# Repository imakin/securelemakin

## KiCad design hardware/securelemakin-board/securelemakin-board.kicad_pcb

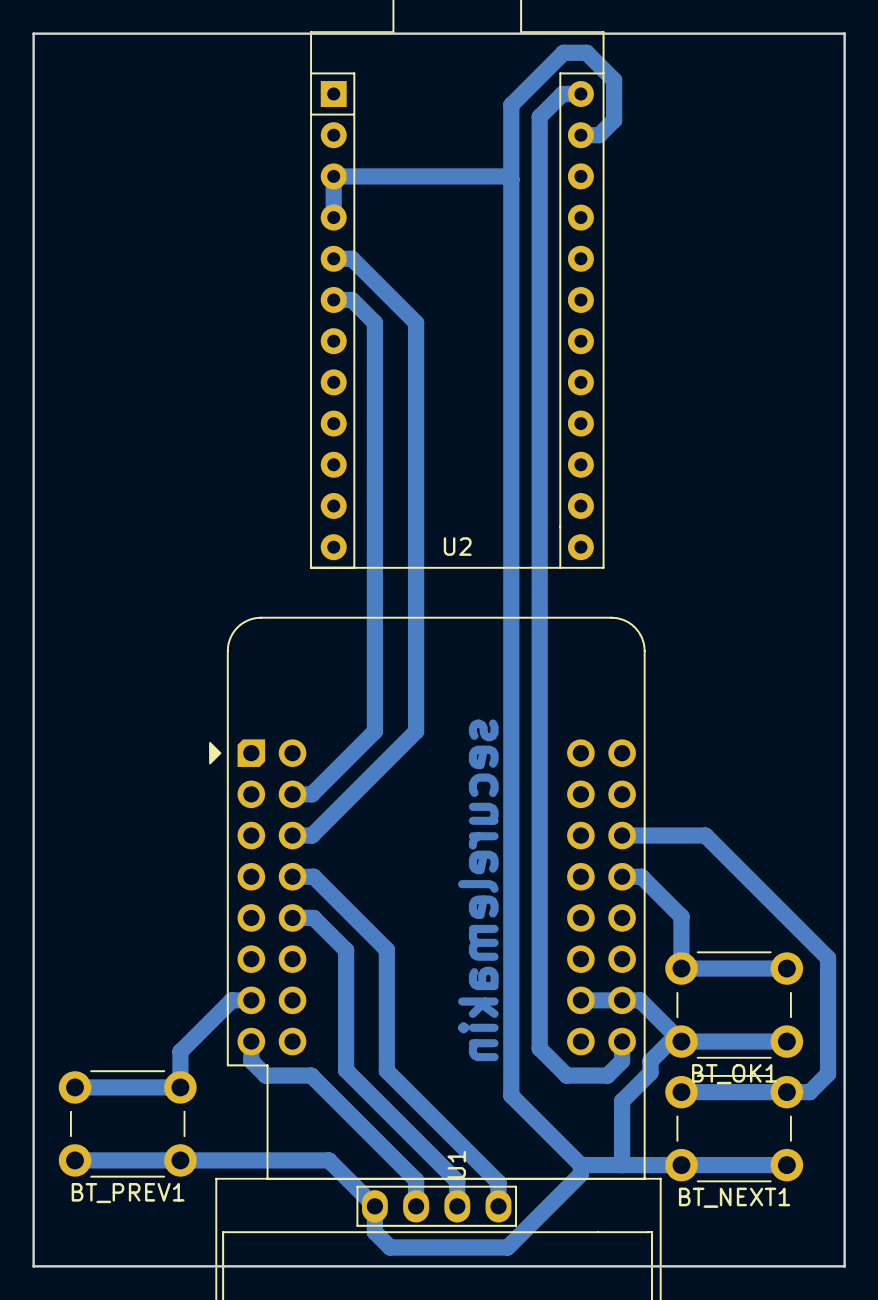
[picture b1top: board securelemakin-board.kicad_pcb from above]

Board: 2 copper layers, 50.0 x 76.0 mm, 6 parts (0 on the bottom side), 10 nets.

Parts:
BT_NEXT1: SW_Push; SW_PUSH_6mm
BT_OK1: SW_Push; SW_PUSH_6mm
BT_PREV1: SW_Push; SW_PUSH_6mm
Brd1: SSD1306; 128x64OLED
U1: WeMos_S2_mini; WEMOS_S2_mini
U2: Sparkfun_Pro_Micro

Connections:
/SCL: U1.18 (GPIO2), U2.6 (~D3)
/SCL_SSD1306: Brd1.3 (SCL), U1.21 (GPIO8)
/SDA: U1.19 (GPIO4), U2.5 (D2)
/SDA_SSD1306: Brd1.4 (SDA), U1.20 (GPIO6)
Earth: BT_NEXT1.1, BT_OK1.1, BT_PREV1.1, Brd1.1 (GND), U1.10 (GND), U1.26 (GND), U2.3 (GND), U2.4 (GND), U2.23 (GND)
unnamed: Brd1.2 (VCC), U1.8 (3V3)
unnamed: BT_PREV1.2, U1.7 (GPIO12)
unnamed: BT_OK1.2, U1.13 (GPIO33)
unnamed: BT_NEXT1.2, U1.14 (GPIO35)
unnamed: U1.9 (VBUS), U2.24 (RAW)

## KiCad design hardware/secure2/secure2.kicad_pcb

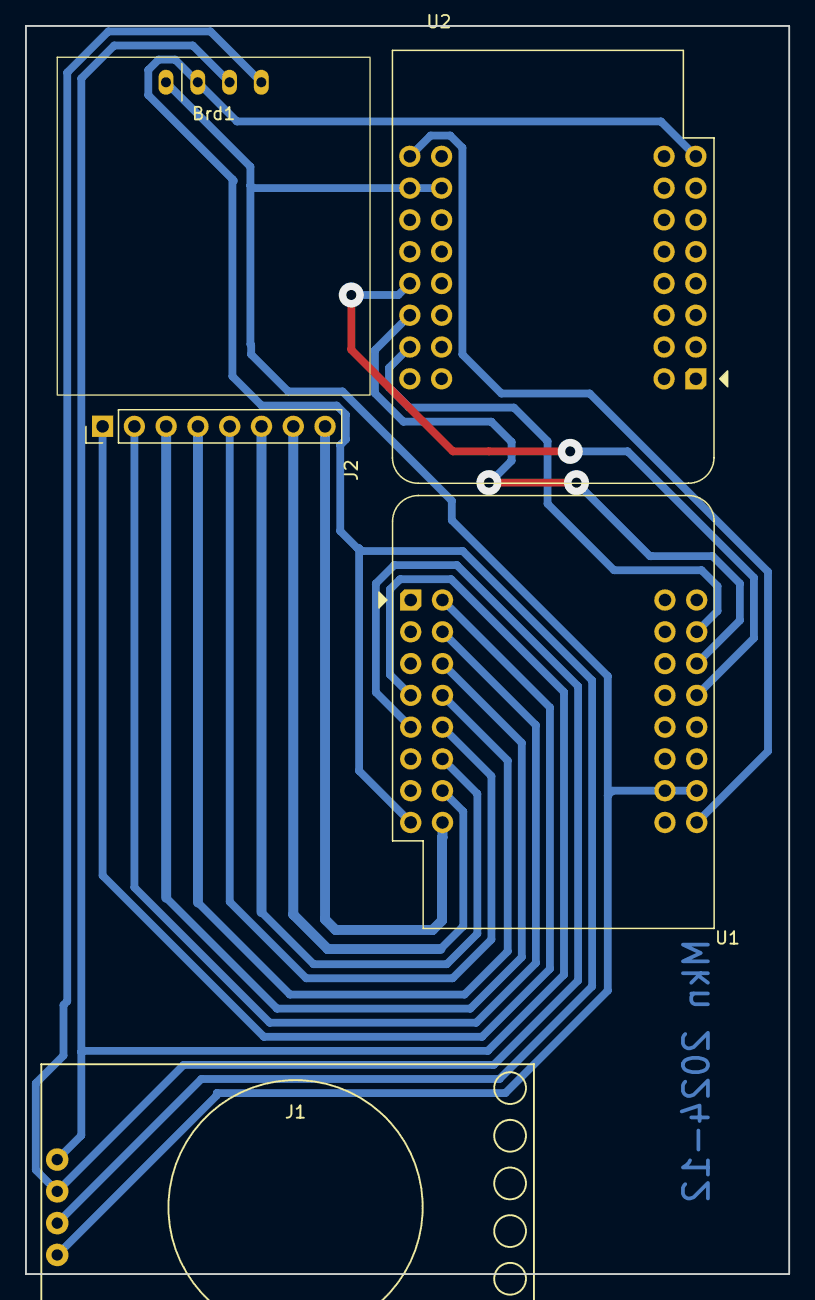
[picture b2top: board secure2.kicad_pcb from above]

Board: 2 copper layers, 61.0 x 99.8 mm, 5 parts (0 on the bottom side), 16 nets.

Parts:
Brd1: SSD1306; ssd1306_128x64oled_module
J1: RTC_DS3231
J2: Buttons; PinHeader_1x08_P2.54mm_Vertical
U1, U2: WeMos_S2_mini; WEMOS_S2_mini

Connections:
+3V3: Brd1.2 (VCC), J1.3, U1.8 (3V3), U2.8 (3V3)
+5V: U1.9 (VBUS), U2.9 (VBUS)
/SCL: Brd1.3 (SCL), J1.1, U1.4 (GPIO7)
/SCL_esp2esp: U1.13 (GPIO33), U2.13 (GPIO33)
/SDA: Brd1.4 (SDA), J1.2, U1.5 (GPIO9)
/SDA_esp2esp: U1.14 (GPIO35), U2.14 (GPIO35)
/flag_pin: U1.15 (GPIO37), U2.15 (GPIO37)
GND: Brd1.1 (GND), J1.4, U1.10 (GND), U1.26 (GND), U2.10 (GND), U2.26 (GND)
unnamed: J2.1, U1.17 (GPIO1)
unnamed: J2.2, U1.18 (GPIO2)
unnamed: J2.3, U1.19 (GPIO4)
unnamed: J2.4, U1.20 (GPIO6)
unnamed: J2.5, U1.21 (GPIO8)
unnamed: J2.6, U1.22 (GPIO10)
unnamed: J2.7, U1.23 (GPIO13)
unnamed: J2.8, U1.24 (GPIO14)

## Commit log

2023-06-29 add files
2023-06-30 fix onboot library install process
2023-06-30 add on boot default method/api
2023-06-30 add button controlled selection. make minifier upload.py
2023-07-10 complete functionality of serial mode and button mode
2023-07-10 add cmd_encrypt
2023-07-12 add upload popup, add auto select default port, add argument based secure data upload
2023-09-02 increase effectivity
2023-09-02 add gui for desktop
2023-09-02 add kicad hardware
2023-09-07 add esp32 single device variant
2023-09-07 fix mem allocation error, optimize ram usage when reading files
2023-09-28 add esp32s2-double version
2023-09-29 hardware ignore
2023-09-29 html update
2023-09-29 move unused files
2023-09-29 add html link for cmd_print and cmd_otp
2023-09-29 add add data form
2023-10-16 make web interface data addition, with post
2023-10-21 fix when to delay on post request
2023-10-30 make processing/ok information for the post request
2023-11-16 remove i2c routine
2023-12-02 add OTP delay, add search & execute
2024-01-09 add small prime asymetric encrypt for data transfer
2024-03-21 add link to enc.py as reusable
2024-04-09 add linux securelemakin
2024-04-09 minor config update
2024-04-09 add data manager
2024-04-09 update gitignore
2024-04-09 add reusable totp pyboard
2024-04-09 add symlink to datamanager
2024-04-18 add url /list menu use face auth add menu maker (linux)
2024-09-09 asymetryclight update, linux typer add displayo
2024-09-09 remove unused code and update comments
2024-10-07 use different port to support joystick and oled display
2024-10-07 update tools
2024-10-07 linux app use pynput now to (partially) support wayland
2025-01-16 now use rtc module for time used in otp. add sleep/delay command in secure data
2025-01-16 add PCB files
2026-01-12 update upload
2026-01-12 update enc3 (chacha20 with randomize nonce)
